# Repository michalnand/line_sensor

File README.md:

# i2c sensor for line follower

- 10x analog readed sensor
- stm32g031k8u6 64MHz arm cortex m0+ mcu
- i2c interface, with FFC cable
- uart, swdio availible for debug

# photos

TODO

# hardware basic

# hardware slim

# arduino example - minimal code

link to file : [demo_code](examples/arduino/minimal_test/minimal_test.ino)

## example output 

- device i2c address is 7bit, 0x42
- in setup, program prints readed  who am I, must be readed as **171** (dec 171) if connected correctly
- program prints LS_DIF_FIL_REG reading : filtered differences of on / off leds readings

```bash
who am i reg : 171
0 6 0 0 598 27 3307 3303 3305 3299 
11 6 0 0 560 3 0 0 0 0 
0 2 2 0 594 86 20 7 0 0 
0 3 4 0 594 87 21 7 1 0 
0 4 2 0 594 88 20 5 1 0 
11 5 0 0 562 0 0 0 0 0 
0 3 4 0 596 87 19 7 2 0 
0 6 4 0 594 86 19 6 2 0 
```

# arduino example - full reading

link to file : [demo_code](examples/arduino/full_test/full_test.ino)

## example output

- device i2c address is 7bit, 0x42
- who am I must be readed as **171** (dec 171)
- readings per second : arround 1800 .. 2000, with 100kHz default arduino i2c speed
- readed data :
  - line 1 : led turned off readings, register LS_RAW_OFF_REG
  - line 2 : led turned in readings, register LS_RAW_ON_REG
  - line 3 : led turned off low pass filtered readings, register LS_FIL_OFF_REG
  - line 4 : led turned in low pass filtered readings, register LS_FIL_ON_REG
  - line 5 : raw readings difference, register LS_DIF_RAW_REG
  - line 6 : filtered readings difference, register LS_DIF_FIL_REG
- in practice, only reading from LS_DIF_FIL_REG (or LS_DIF_RAW_REG) is necessary to estimate line position

```bash
who am i reg : 171
readings per second 2000
readed data
1206 1467 1156 1393 3102 1862 1558 1523 1559 1495 
1206 1464 1139 1365 815 1351 1501 1515 1567 1280 
1205 1467 1152 1390 3087 1851 1552 1520 1556 1494 
1203 1461 1136 1361 810 1349 1501 1515 1563 1280 
7 7 10 36 2253 464 39 1 0 0 
0 6 16 30 2269 543 68 17 3 0 
```

# usage

## compiling firmware

- arm-none-eabi-gcc is required

```bash
cd firmware
make clean
make
```

## writing into flash

- use st-link for write firmware
- connect gnd, swclk, swdio and reset to debug connector
- execture **st-flash --connect-under-reset write build.bin 0x8000000**

```bash
cd firmware/bin
./arm_burn
```

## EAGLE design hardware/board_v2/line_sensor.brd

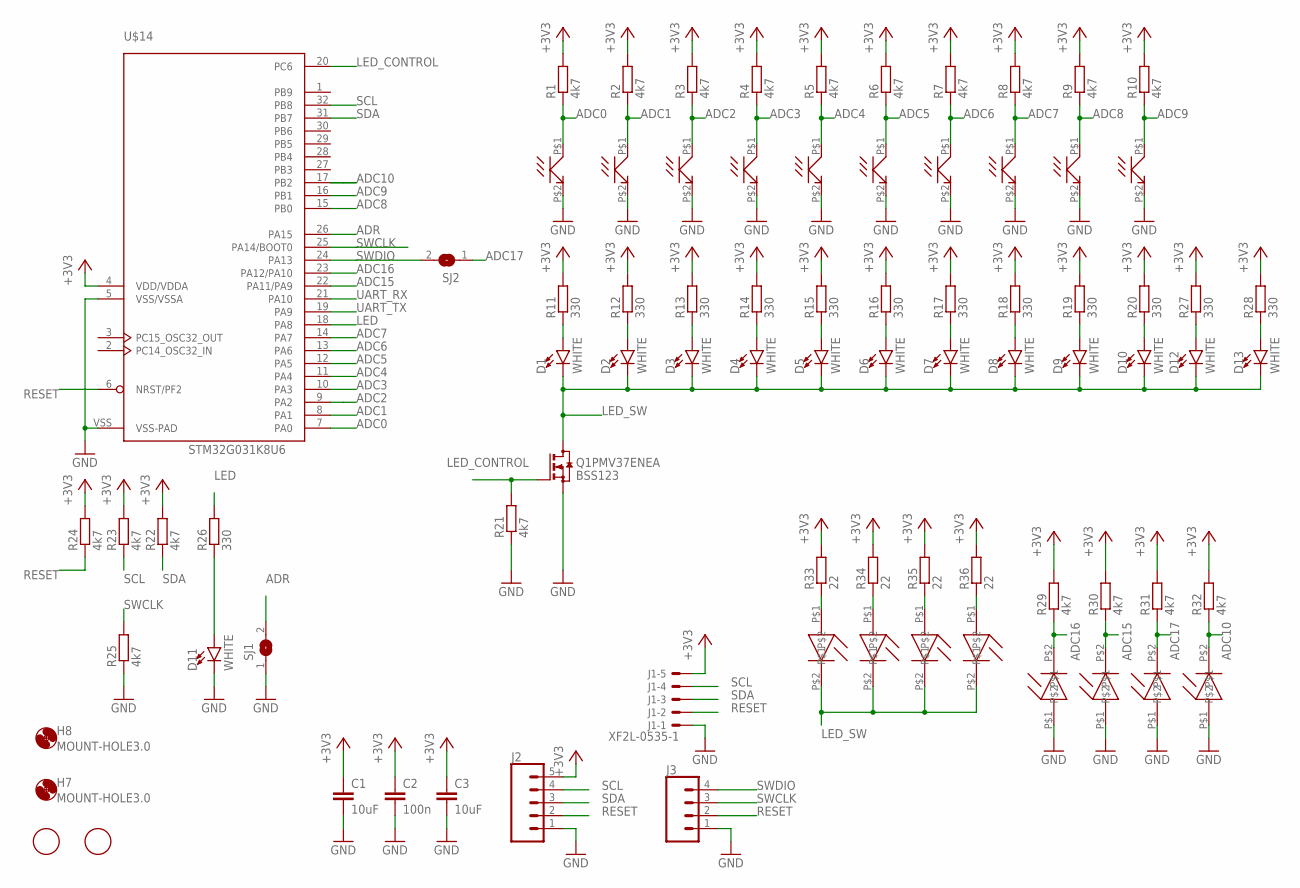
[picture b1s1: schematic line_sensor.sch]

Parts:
C1, C3: 10uF; C0805K
C2: 100n; C0805K
D1, D2, D3, D4, D5, D6, D7, D8, D9, D10, D11, D12, D13: WHITE; LED-1206
H7, H8: MOUNT-HOLE3.0; 3,0
J1: XF2L-0535-1
J2: CONN_05; 1X05
J3: CONN_04LOCK; 1X04_LOCK
Q1PMV37ENEA: BSS123; SOT23
R1, R2, R3, R4, R5, R6, R7, R8, R9, R10, R21, R22, R23, R24, R25, R29, R30, R31, R32: 4k7; M0805
R11, R12, R13, R14, R15, R16, R17, R18, R19, R20, R26, R27, R28: 330; M0805
R33, R34, R35, R36: 22; M0805
SJ1, SJ2: SJ
U$1, U$2, U$3, U$4, U$5, U$6, U$7, U$8, U$9, U$10: SFH3710; SFH710
U$11, U$15, U$16, U$17, U$18, U$19, U$20, U$21: LED_5MM_AXIAL
U$12, U$13: FIDUCIAL; FIDUCIAL_1MM
U$14: STM32G031K8U6; UFQFPN32

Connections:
+3V3: C1.1, C2.1, C3.1, J1.5 (MS), J2.5, R1.2, R2.2, R3.2, R4.2, R5.2, R6.2, R7.2, R8.2, R9.2, R10.2, R11.2, R12.2, R13.2, R14.2, R15.2, R16.2, R17.2, R18.2, R19.2, R20.2, R22.2, R23.2, R24.2, R27.2, R28.2, R29.2, R30.2, R31.2, R32.2, R33.2, R34.2, R35.2, R36.2, U$14.4 (VDD/VDDA)
ADC0: R1.1, U$1.P$1 (C), U$14.7 (PA0)
ADC1: R2.1, U$2.P$1 (C), U$14.8 (PA1)
ADC2: R3.1, U$3.P$1 (C), U$14.9 (PA2)
ADC3: R4.1, U$4.P$1 (C), U$14.10 (PA3)
ADC4: R5.1, U$5.P$1 (C), U$14.11 (PA4)
ADC5: R6.1, U$6.P$1 (C), U$14.12 (PA5)
ADC6: R7.1, U$7.P$1 (C), U$14.13 (PA6)
ADC7: R8.1, U$8.P$1 (C), U$14.14 (PA7)
ADC8: R9.1, U$9.P$1 (C), U$14.15 (PB0)
ADC9: R10.1, U$10.P$1 (C), U$14.16 (PB1)
ADC10: R32.1, U$14.17 (PB2), U$21.P$2
ADC15: R30.1, U$14.22 (PA11/PA9), U$17.P$2
ADC16: R29.1, U$14.23 (PA12/PA10), U$15.P$2
ADC17: R31.1, SJ2.1, U$19.P$2
ADR: SJ1.2, U$14.26 (PA15)
GND: C1.2, C2.2, C3.2, D11.C, J1.1 (MSV), J2.1, J3.1, Q1PMV37ENEA.2 (S), R21.1, R25.1, SJ1.1, U$1.P$2 (E), U$2.P$2 (E), U$3.P$2 (E), U$4.P$2 (E), U$5.P$2 (E), U$6.P$2 (E), U$7.P$2 (E), U$8.P$2 (E), U$9.P$2 (E), U$10.P$2 (E), U$14.5 (VSS/VSSA), U$14.VSS (VSS-PAD), U$15.P$1, U$17.P$1, U$19.P$1, U$21.P$1
LED: R26.2, U$14.18 (PA8)
LED_CONTROL: Q1PMV37ENEA.1 (G), R21.2, U$14.20 (PC6)
LED_SW: D1.C, D2.C, D3.C, D4.C, D5.C, D6.C, D7.C, D8.C, D9.C, D10.C, D12.C, D13.C, Q1PMV37ENEA.3 (D), U$11.P$2, U$16.P$2, U$18.P$2, U$20.P$2
unnamed: D1.A, R11.1
unnamed: D2.A, R12.1
unnamed: D3.A, R13.1
unnamed: D4.A, R14.1
unnamed: D5.A, R15.1
unnamed: D6.A, R16.1
unnamed: D7.A, R17.1
unnamed: D8.A, R18.1
unnamed: D9.A, R19.1
unnamed: D10.A, R20.1
unnamed: R33.1, U$11.P$1
unnamed: D11.A, R26.1
unnamed: D12.A, R27.1
unnamed: D13.A, R28.1
unnamed: R34.1, U$16.P$1
unnamed: R35.1, U$18.P$1
unnamed: R36.1, U$20.P$1
RESET: J1.2 (MS), J2.2, J3.2, R24.1, U$14.6 (NRST/PF2)
SCL: J1.4 (MS), J2.4, R23.1, U$14.32 (PB8)
SDA: J1.3 (MS), J2.3, R22.1, U$14.31 (PB7)
SWCLK: J3.3, R25.2, U$14.25 (PA14/BOOT0)
SWDIO: J3.4, SJ2.2, U$14.24 (PA13)
UART_RX: U$14.21 (PA10)
UART_TX: U$14.19 (PA9)

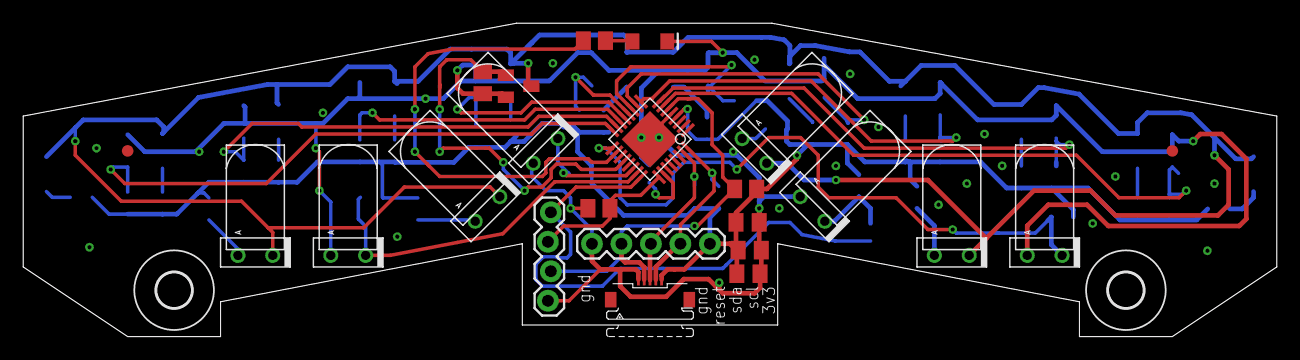
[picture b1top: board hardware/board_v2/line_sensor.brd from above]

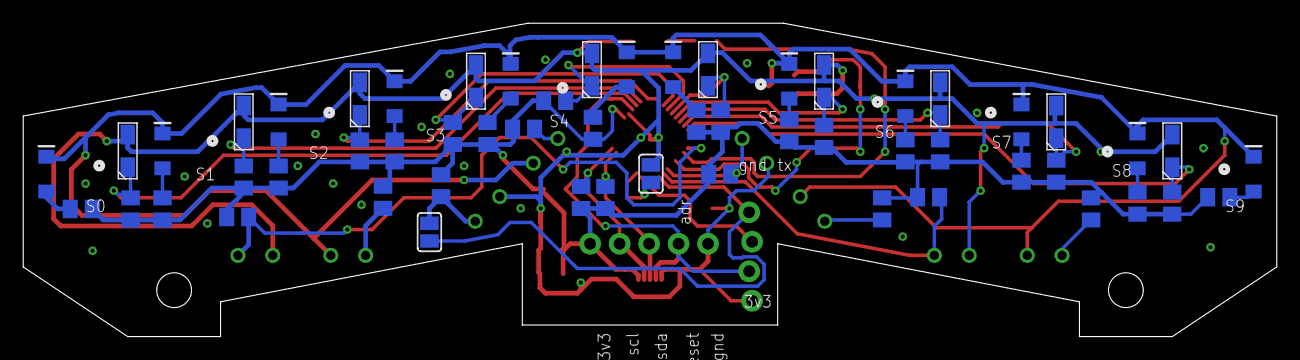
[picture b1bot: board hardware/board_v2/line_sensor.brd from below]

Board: 2 copper layers, 108.0 x 27.0 mm, 81 parts (56 on the bottom side), 42 nets.

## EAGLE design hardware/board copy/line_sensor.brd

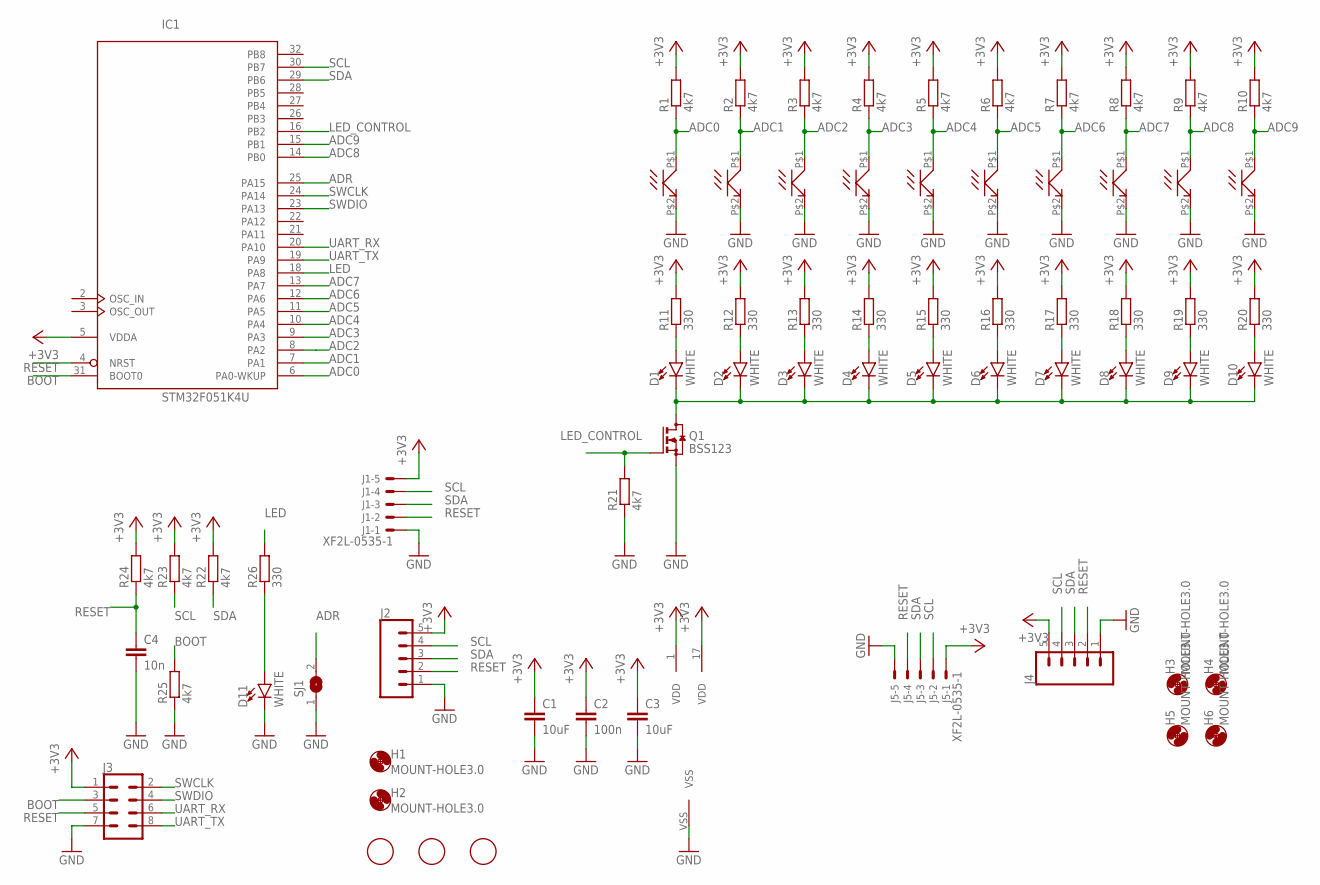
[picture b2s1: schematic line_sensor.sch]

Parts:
C1, C3: 10uF; C0805K
C2: 100n; C0805K
C4: 10n; C0805K
D1, D2, D3, D4, D5, D6, D7, D8, D9, D10, D11: WHITE; LED-1206
H1, H2, H3, H4, H5, H6: MOUNT-HOLE3.0; 3,0
IC1: STM32F051K4U; UFQFPN32
J1, J5: XF2L-0535-1
J2, J4: CONN_05; 1X05
J3: CONN_04X2; 2X4
Q1: BSS123; SOT23
R1, R2, R3, R4, R5, R6, R7, R8, R9, R10, R21, R22, R23, R24, R25: 4k7; M0805
R11, R12, R13, R14, R15, R16, R17, R18, R19, R20, R26: 330; M0805
SJ1: SJ
U$1, U$2, U$3, U$4, U$5, U$6, U$7, U$8, U$9, U$10: SFH3710; SFH710
U$11, U$12, U$13: FIDUCIAL; FIDUCIAL_1MM

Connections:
+3V3: C1.1, C2.1, C3.1, IC1.1 (VDD), IC1.5 (VDDA), IC1.17 (VDD), J1.5 (MS), J2.5, J3.1, J4.5, J5.1 (MSV), R1.2, R2.2, R3.2, R4.2, R5.2, R6.2, R7.2, R8.2, R9.2, R10.2, R11.2, R12.2, R13.2, R14.2, R15.2, R16.2, R17.2, R18.2, R19.2, R20.2, R22.2, R23.2, R24.2
ADC0: IC1.6 (PA0-WKUP), R1.1, U$1.P$1 (C)
ADC1: IC1.7 (PA1), R2.1, U$2.P$1 (C)
ADC2: IC1.8 (PA2), R3.1, U$3.P$1 (C)
ADC3: IC1.9 (PA3), R4.1, U$4.P$1 (C)
ADC4: IC1.10 (PA4), R5.1, U$5.P$1 (C)
ADC5: IC1.11 (PA5), R6.1, U$6.P$1 (C)
ADC6: IC1.12 (PA6), R7.1, U$7.P$1 (C)
ADC7: IC1.13 (PA7), R8.1, U$8.P$1 (C)
ADC8: IC1.14 (PB0), R9.1, U$9.P$1 (C)
ADC9: IC1.15 (PB1), R10.1, U$10.P$1 (C)
ADR: IC1.25 (PA15), SJ1.2
BOOT: IC1.31 (BOOT0), J3.3, R25.2
GND: C1.2, C2.2, C3.2, C4.2, D11.C, IC1.VSS, J1.1 (MSV), J2.1, J3.7, J4.1, J5.5 (MS), Q1.2 (S), R21.1, R25.1, SJ1.1, U$1.P$2 (E), U$2.P$2 (E), U$3.P$2 (E), U$4.P$2 (E), U$5.P$2 (E), U$6.P$2 (E), U$7.P$2 (E), U$8.P$2 (E), U$9.P$2 (E), U$10.P$2 (E)
LED: IC1.18 (PA8), R26.2
LED_CONTROL: IC1.16 (PB2), Q1.1 (G), R21.2
unnamed: D1.A, R11.1
unnamed: D2.A, R12.1
unnamed: D3.A, R13.1
unnamed: D4.A, R14.1
unnamed: D5.A, R15.1
unnamed: D6.A, R16.1
unnamed: D7.A, R17.1
unnamed: D8.A, R18.1
unnamed: D9.A, R19.1
unnamed: D10.A, R20.1
unnamed: D1.C, D2.C, D3.C, D4.C, D5.C, D6.C, D7.C, D8.C, D9.C, D10.C, Q1.3 (D)
unnamed: D11.A, R26.1
RESET: C4.1, IC1.4 (NRST), J1.2 (MS), J2.2, J3.5, J4.2, J5.4 (MS), R24.1
SCL: IC1.30 (PB7), J1.4 (MS), J2.4, J4.4, J5.2 (MS), R23.1
SDA: IC1.29 (PB6), J1.3 (MS), J2.3, J4.3, J5.3 (MS), R22.1
SWCLK: IC1.24 (PA14), J3.2
SWDIO: IC1.23 (PA13), J3.4
UART_RX: IC1.20 (PA10), J3.6
UART_TX: IC1.19 (PA9), J3.8

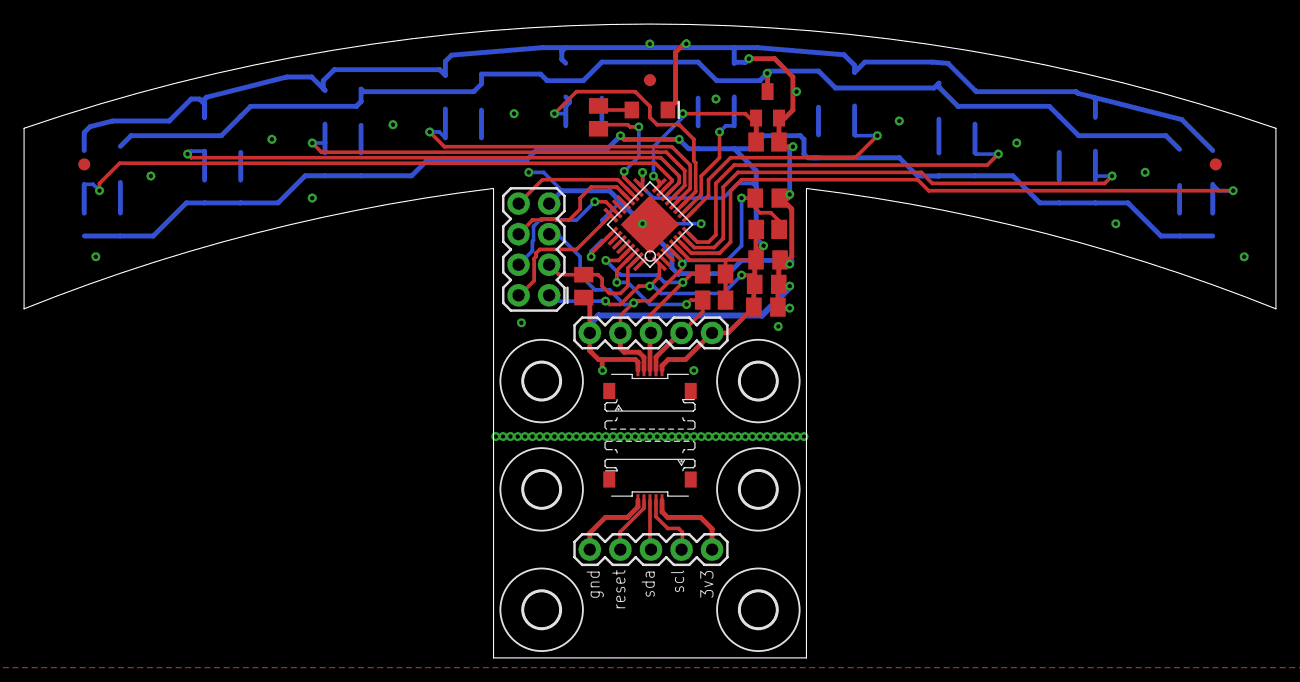
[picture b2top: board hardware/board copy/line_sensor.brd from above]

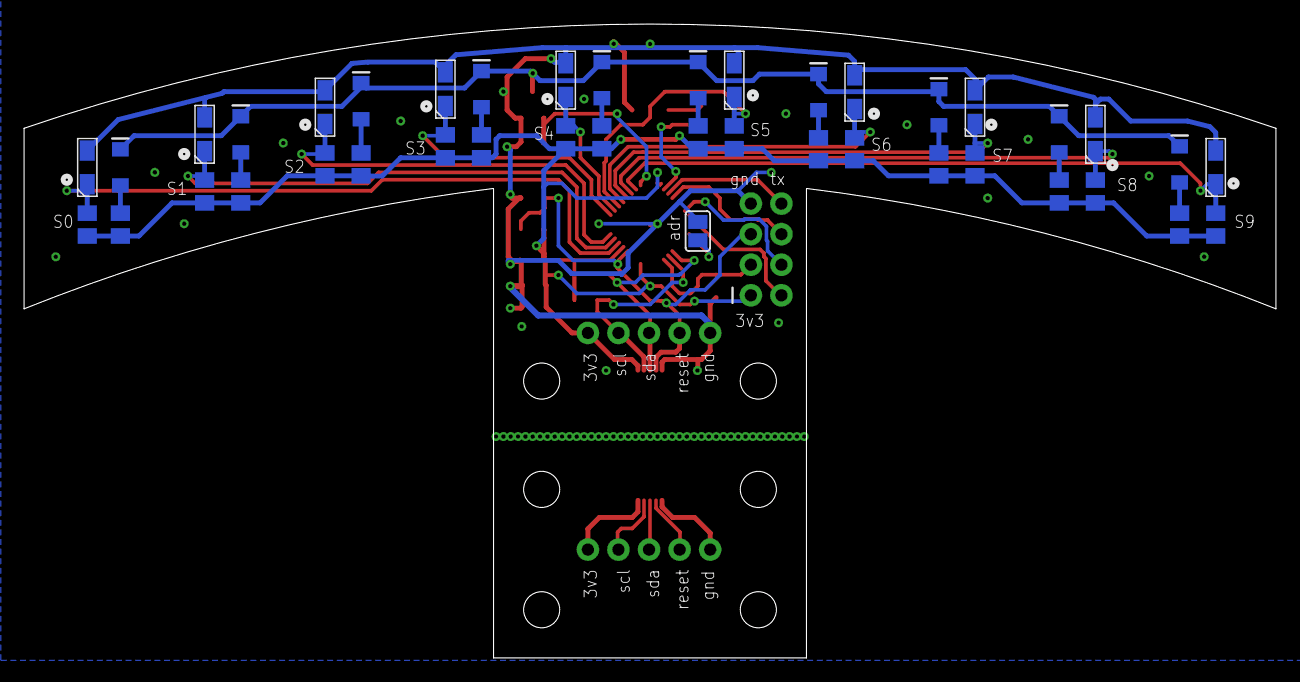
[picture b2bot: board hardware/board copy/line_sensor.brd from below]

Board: 2 copper layers, 104.0 x 52.7 mm, 68 parts (41 on the bottom side), 35 nets.

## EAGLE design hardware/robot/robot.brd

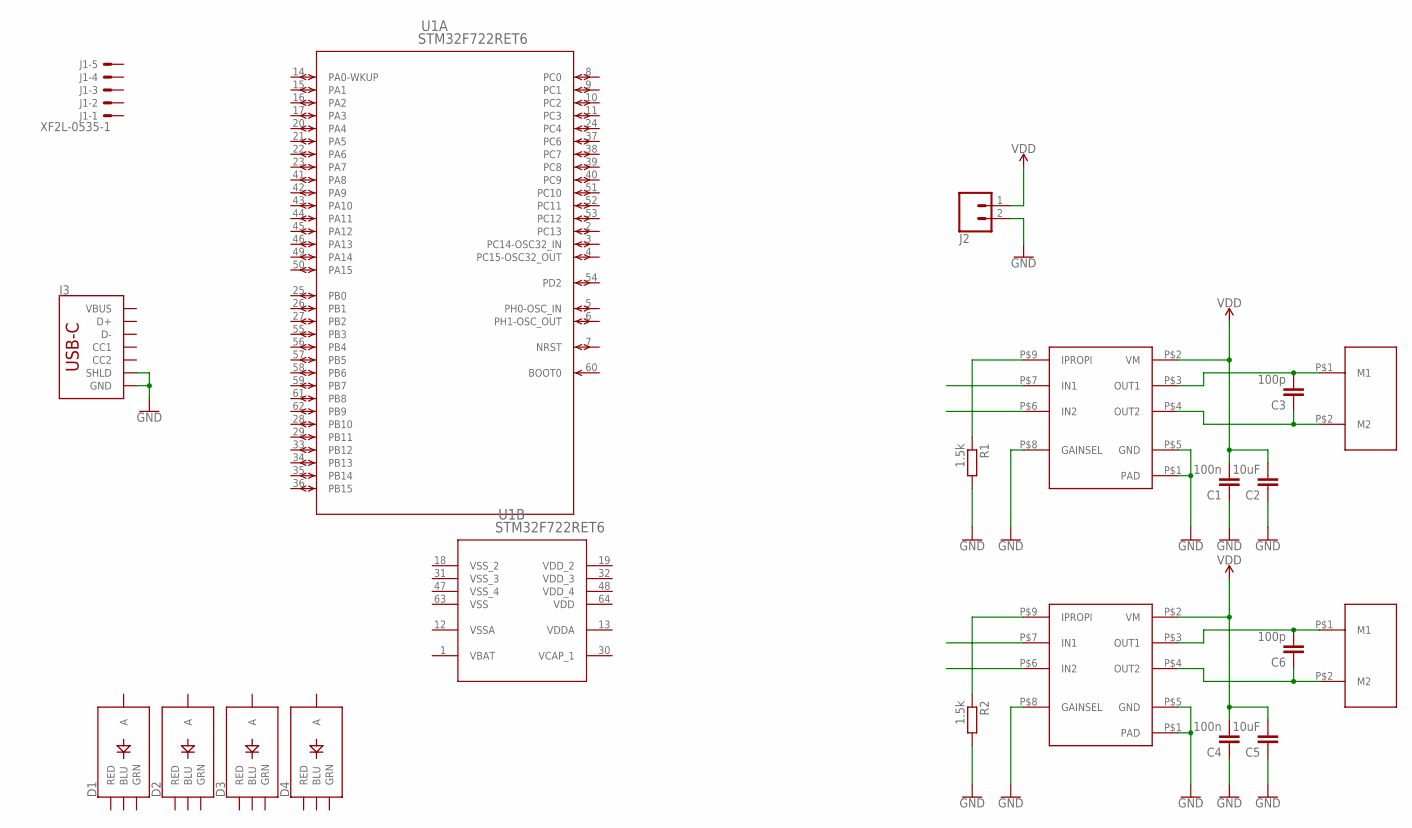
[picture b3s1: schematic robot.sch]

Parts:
C1, C4: 100n; C0805
C2, C5: 10uF; C0805
C3, C6: 100p; C0805
D1, D2, D3, D4: LED-RGB-CASMD; LED-TRICOLOR-SMD
J1: XF2L-0535-1
J2: CONN_02; 1X02
J3: USB_C_2-LAYER_PADS; USB-C-16P-2LAYER-PADS
R1, R2: 1.5k; M0805
U1: STM32F722RET6; LQFP64-10X10MM
U$1, U$2: POLOLU_MICRO_METAL_GEAR_MOTOR
U$3, U$4: DRV8213; DSG8

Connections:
GND: C1.1, C2.1, C4.1, C5.1, J2.2, J3.GND, J3.GND2 (GND), J3.SHLD1 (SHLD), J3.SHLD2 (SHLD), J3.SHLD3 (SHLD), J3.SHLD4 (SHLD), R1.2, R2.2, U$3.P$1 (PAD), U$3.P$5 (GND), U$3.P$8 (GAINSEL), U$4.P$1 (PAD), U$4.P$5 (GND), U$4.P$8 (GAINSEL)
unnamed: R1.1, U$3.P$9 (IPROPI)
unnamed: C3.1, U$1.P$2 (M2), U$3.P$4 (OUT2)
unnamed: C3.2, U$1.P$1 (M1), U$3.P$3 (OUT1)
unnamed: R2.1, U$4.P$9 (IPROPI)
unnamed: C6.1, U$2.P$2 (M2), U$4.P$4 (OUT2)
unnamed: C6.2, U$2.P$1 (M1), U$4.P$3 (OUT1)
VBAT: U1.1 (VBAT)
VCAP_1: U1.30 (VCAP_1)
VDD: C1.2, C2.2, C4.2, C5.2, J2.1, U1.64 (VDD), U$3.P$2 (VM), U$4.P$2 (VM)
VDDA: U1.13 (VDDA)
VDD_2: U1.19 (VDD_2)
VDD_3: U1.32 (VDD_3)
VDD_4: U1.48 (VDD_4)
VSS: U1.63 (VSS)
VSSA: U1.12 (VSSA)
VSS_2: U1.18 (VSS_2)
VSS_3: U1.31 (VSS_3)
VSS_4: U1.47 (VSS_4)

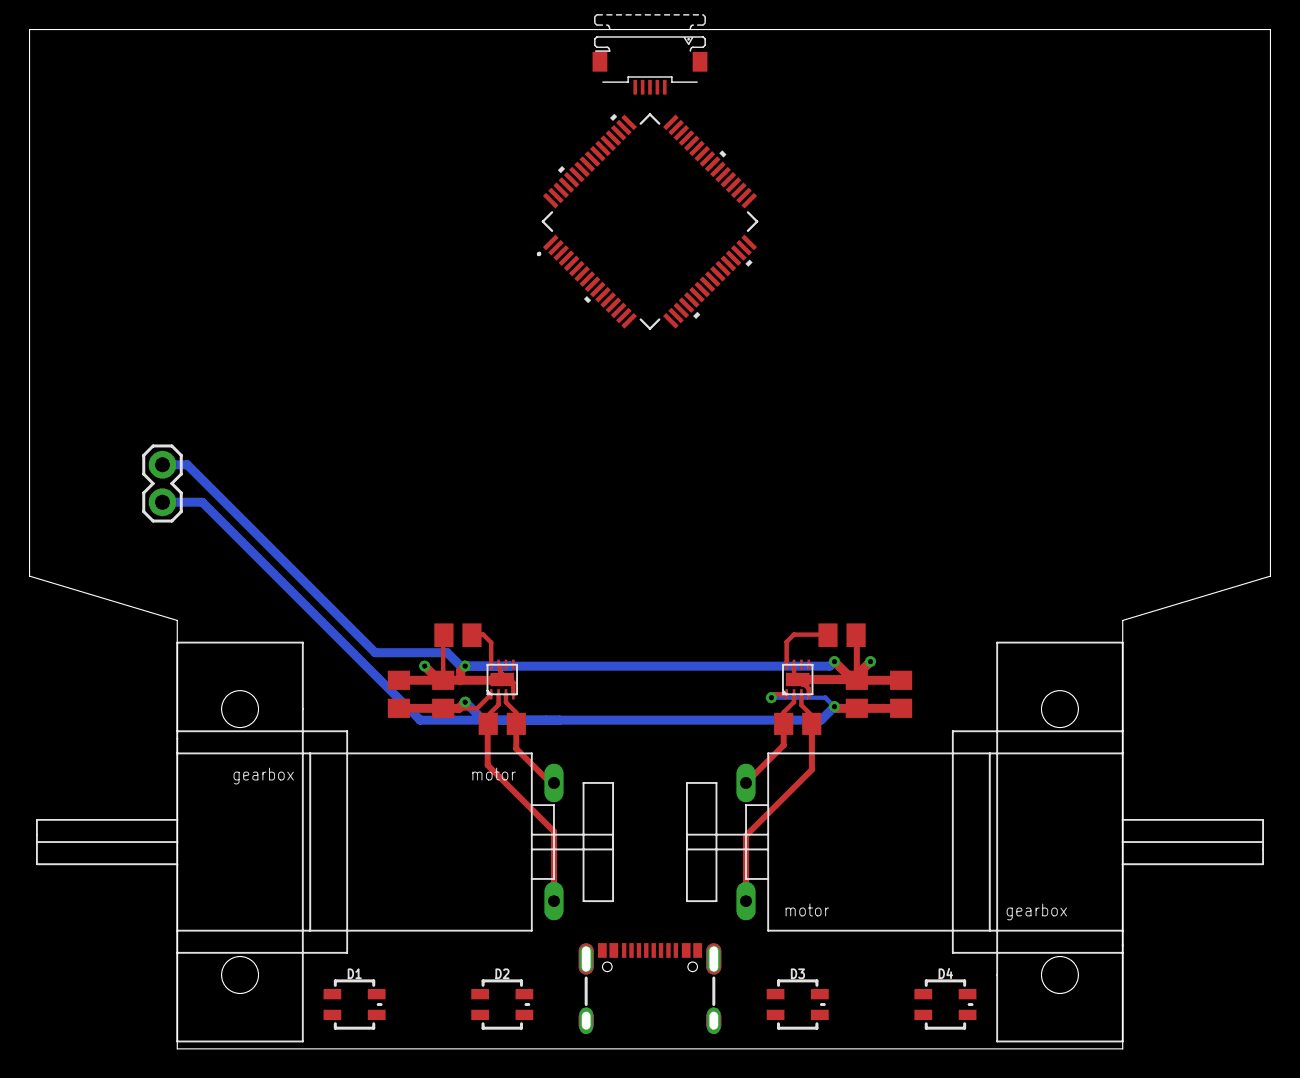
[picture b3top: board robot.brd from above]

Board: 2 copper layers, 83.4 x 68.4 mm, 20 parts (0 on the bottom side), 8 nets.

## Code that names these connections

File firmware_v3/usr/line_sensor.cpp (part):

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        if (this->led_state == true)
        {
            this->led_state = false;
            this->led_control = 0;
        }
        
        else
        {
            this->led_state = true;
            this->led_control = 1;
        }
       
        // initial state for next round 
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
void LineSensor::_init_vars()
{
    this->led_control   = 0;
    
    this->state         = 0;
    this->led_state     = false;
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    LL_IOP_GRP1_EnableClock(LL_IOP_GRP1_PERIPH_GPIOC);

        
    // Configure PA0 - PA7 as analog (ADC_IN0 to ADC_IN7)
    LL_GPIO_SetPinMode(GPIOA, LL_GPIO_PIN_0, LL_GPIO_MODE_ANALOG);
    LL_GPIO_SetPinPull(GPIOA, LL_GPIO_PIN_0, LL_GPIO_PULL_NO);

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    LL_GPIO_SetPinMode(GPIOA, LL_GPIO_PIN_7, LL_GPIO_MODE_ANALOG);
    LL_GPIO_SetPinPull(GPIOA, LL_GPIO_PIN_7, LL_GPIO_PULL_NO);  

    // Configure PB0, PB1 as analog (ADC_IN8, ADC_IN9)
    LL_GPIO_SetPinMode(GPIOB, LL_GPIO_PIN_0, LL_GPIO_MODE_ANALOG);
    LL_GPIO_SetPinPull(GPIOB, LL_GPIO_PIN_0, LL_GPIO_PULL_NO);

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    LL_GPIO_SetPinPull(GPIOB, LL_GPIO_PIN_1, LL_GPIO_PULL_NO);


    // Configure PA11, PA12, PA13 as analog (ADC_IN15, ADC_IN16, ADC_IN17)
    LL_GPIO_SetPinMode(GPIOA, LL_GPIO_PIN_11, LL_GPIO_MODE_ANALOG);
    LL_GPIO_SetPinPull(GPIOA, LL_GPIO_PIN_11, LL_GPIO_PULL_NO);
    
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    LL_GPIO_SetPinMode(GPIOA, LL_GPIO_PIN_13, LL_GPIO_MODE_ANALOG);
    LL_GPIO_SetPinPull(GPIOA, LL_GPIO_PIN_13, LL_GPIO_PULL_NO);

    // Configure PB2 as analog (ADC_IN10)   
    LL_GPIO_SetPinMode(GPIOB, LL_GPIO_PIN_2, LL_GPIO_MODE_ANALOG);
    LL_GPIO_SetPinPull(GPIOB, LL_GPIO_PIN_2, LL_GPIO_PULL_NO);

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
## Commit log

2025-05-10 initial
2025-05-11 adc + filter
2025-05-11 led modulation modes
2025-05-11 3d parts
2025-05-12 diagram
2025-05-13 diagrams
2025-05-14 adc bug fix
2025-05-18 i2c slave - bugs on stm32f0
2025-05-24 new hw, firmware for stm32g031
2025-05-24 adc running
2025-05-26 i2c slave
2025-05-27 i2c bug fixed
2025-05-27 arduino example
2025-05-28 working firmware v1
2025-05-31 demo codes, cleaned up
2025-06-15 updated v2 firmware
2025-07-06 docu
2026-02-08 v3 firmware, working as alternate mode only

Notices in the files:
parts and their libraries:
SparkFun-Connectors: Licensing: Creative Commons ShareAlike 4.0 International - https://creativecommons.org/licenses/by-sa/4.0
COPYRIGHT: Copyright (C) 2024 Ultra Librarian. All rights reserved.
